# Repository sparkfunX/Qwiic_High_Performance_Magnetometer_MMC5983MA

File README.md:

# SparkX MMC5983MA Magnetometer Breakout

<p align="center">

</p>

*[SparkX Triple Axis Magnetometer - MMC5983MA (Qwiic) (SPX-19034)](https://www.sparkfun.com/products/19034)*

The MMC5983MA is a highly sensitive triple axis magnetometer by MEMSIC.
It is capable of sensing down to 0.4mG enabling a heading accuracy of ±0.5°.
Output rates of 1000Hz, ±8G FSR, and 18-bit resolution make the MMC5983MA a phenomenal magnetic sensor for electronic compass applications.

### Important Note:

An updated version of this product is available:

*[SparkFun 9DoF IMU Breakout - ISM330DHCX, MMC5983MA (Qwiic) (SEN-19895)](https://www.sparkfun.com/products/19895)*

*[SparkFun Micro Magnetometer - MMC5983MA (Qwiic) (SEN-19921)](https://www.sparkfun.com/products/19921)*

## Repository Contents

* **[/Documents](/Documents/)** - MMC5983MA datasheet
* **[/Hardware](/Hardware/)** - Eagle design files (.brd, .sch)

## Product Versions

* [SPX-19034](https://www.sparkfun.com/products/19034) - Initial SparkX Release

## License Information

This product is _**open source**_! 

Please review the LICENSE.md file for license information. 

If you have any questions or concerns on licensing, please contact technical support on our [SparkFun forums](https://forum.sparkfun.com/viewforum.php?f=152).

Distributed as-is; no warranty is given.

- Your friends at SparkFun.

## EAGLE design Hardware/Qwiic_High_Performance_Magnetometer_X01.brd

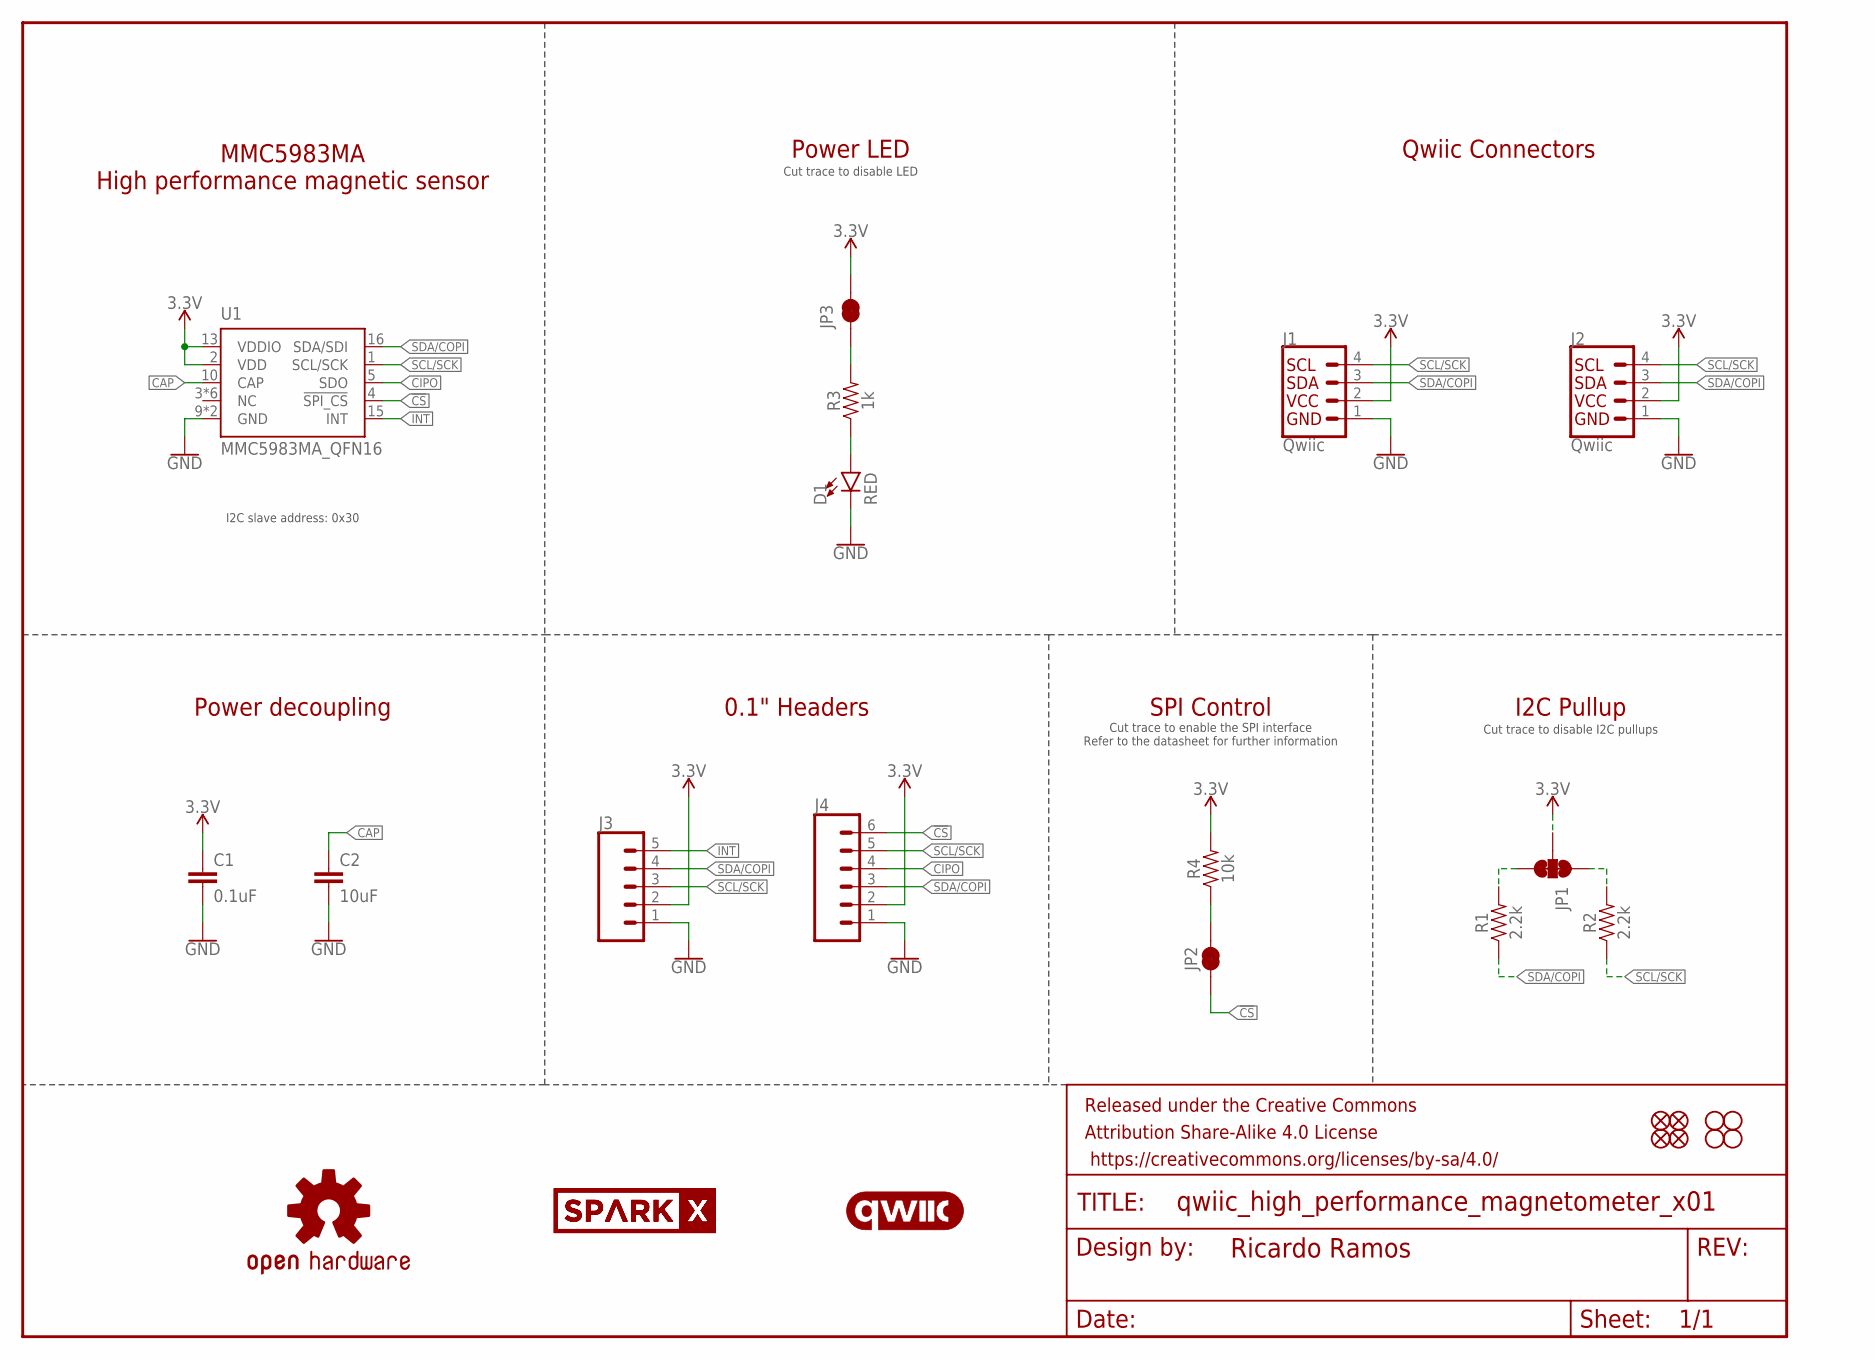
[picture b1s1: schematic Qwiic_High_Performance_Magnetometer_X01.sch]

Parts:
C1: 0.1uF; 0603
C2: 10uF; 0603
D1: RED; LED-0603
FD1, FD2, FD3, FD4: FIDUCIAL1X2; FIDUCIAL-1X2
FRAME1: FRAME-LETTERNO_PACKAGE; DUMMY
H1, H2, H3, H4: STAND-OFF
J1, J2: Qwiic; JST04_1MM_RA
J3: CONN_05NO_SILK; 1X05_NO_SILK
J4: CONN_06NO_SILK_NO_POP; 1X06_NO_SILK
JP1: JUMPER-SMT_3_2-NC_TRACE_SILK; SMT-JUMPER_3_2-NC_TRACE_SILK
JP2, JP3: JUMPER-SMT_2_NC_TRACE_SILK; SMT-JUMPER_2_NC_TRACE_SILK
LOGO1: OSHW-LOGOMINI; OSHW-LOGO-MINI
LOGO2: QWIIC_LOGO_5MM; QWIIC_5MM
R1, R2: 2.2k; 0603
R3: 1k; 0603
R4: 10k; 0603
U1: MMC5983MA_QFN16; LGA-16-3X3MM-4X4PINS
U$36: SPARKX-LOGO2; SPARKX-TINY
U$37: SPARKX-LOGO3; SPARKX-SMALL

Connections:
3.3V: C1.1, J1.2, J2.2, J3.2, J4.2, JP1.2, JP3.2, R4.2, U1.2 (VDD), U1.13 (VDDIO)
!CS!: J4.6, JP2.1, U1.4 (!SPI_CS!)
CAP: C2.1, U1.10 (CAP)
CIPO: J4.4, U1.5 (SDO)
GND: C1.2, C2.2, D1.C, J1.1, J2.1, J3.1, J4.1, U1.9 (GND), U1.11 (GND)
INT: J3.5, U1.15 (INT)
unnamed: JP3.1, R3.2
unnamed: JP1.1, R2.2
unnamed: JP1.3, R1.2
unnamed: D1.A, R3.1
unnamed: JP2.2, R4.1
SCL/SCK: J1.4, J2.4, J3.3, J4.5, R2.1, U1.1 (SCL/SCK)
SDA/COPI: J1.3, J2.3, J3.4, J4.3, R1.1, U1.16 (SDA/SDI)

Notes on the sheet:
Qwiic Connectors
Cut trace to disable LED
0.1" Headers
Power LED
Power decoupling
MMC5983MA High performance magnetic sensor
I2C slave address: 0x30
I2C Pullup
Cut trace to disable I2C pullups
SPI Control
Cut trace to enable the SPI interface Refer to the datasheet for further information

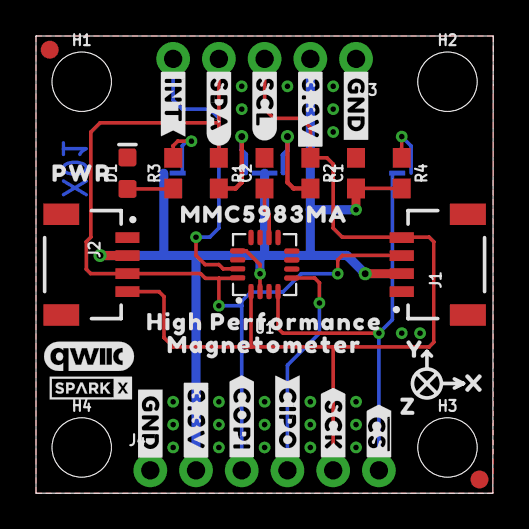
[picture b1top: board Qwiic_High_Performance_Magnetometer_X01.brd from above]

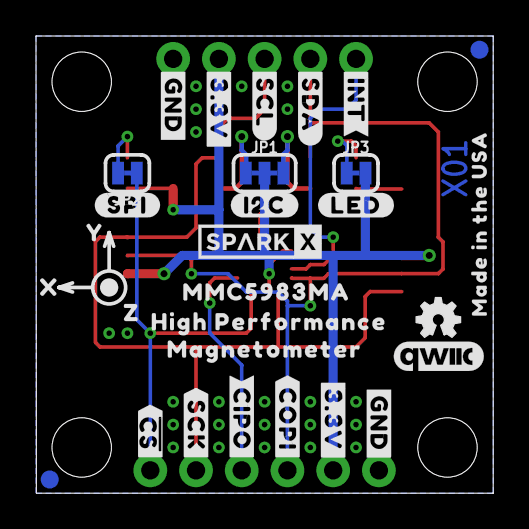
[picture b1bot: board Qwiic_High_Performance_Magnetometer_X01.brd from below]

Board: 2 copper layers, 25.4 x 25.4 mm, 68 parts (29 on the bottom side), 13 nets.

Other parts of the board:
LOGO3: QWIIC_LOGO_5MM; QWIIC_5MM
U$1, U$10: HIGH_PERFORMANCE11
U$2, U$35: #SCL#6
U$3, U$12, U$18, U$29: #3#3V#0
U$4, U$13, U$17, U$28: #GND#4
U$5, U$38: #SDA#5
U$6, U$31: #CIPO#11
U$7, U$16: #INT#7
U$8: PWR9
U$9, U$30: #COPI#12
U$11, U$24: MAGNETOMETER12
U$14, U$32: #SCK#13
U$15, U$33: ##CS##10
U$19, U$26: Y16
U$20, U$25: X15
U$21: #LED#8
U$22: #I2C#9
U$23: #SPI#9
U$27, U$39: Z17
U$34: MADE_IN_THE_USA20
U$41, U$42: MMC5983MA0

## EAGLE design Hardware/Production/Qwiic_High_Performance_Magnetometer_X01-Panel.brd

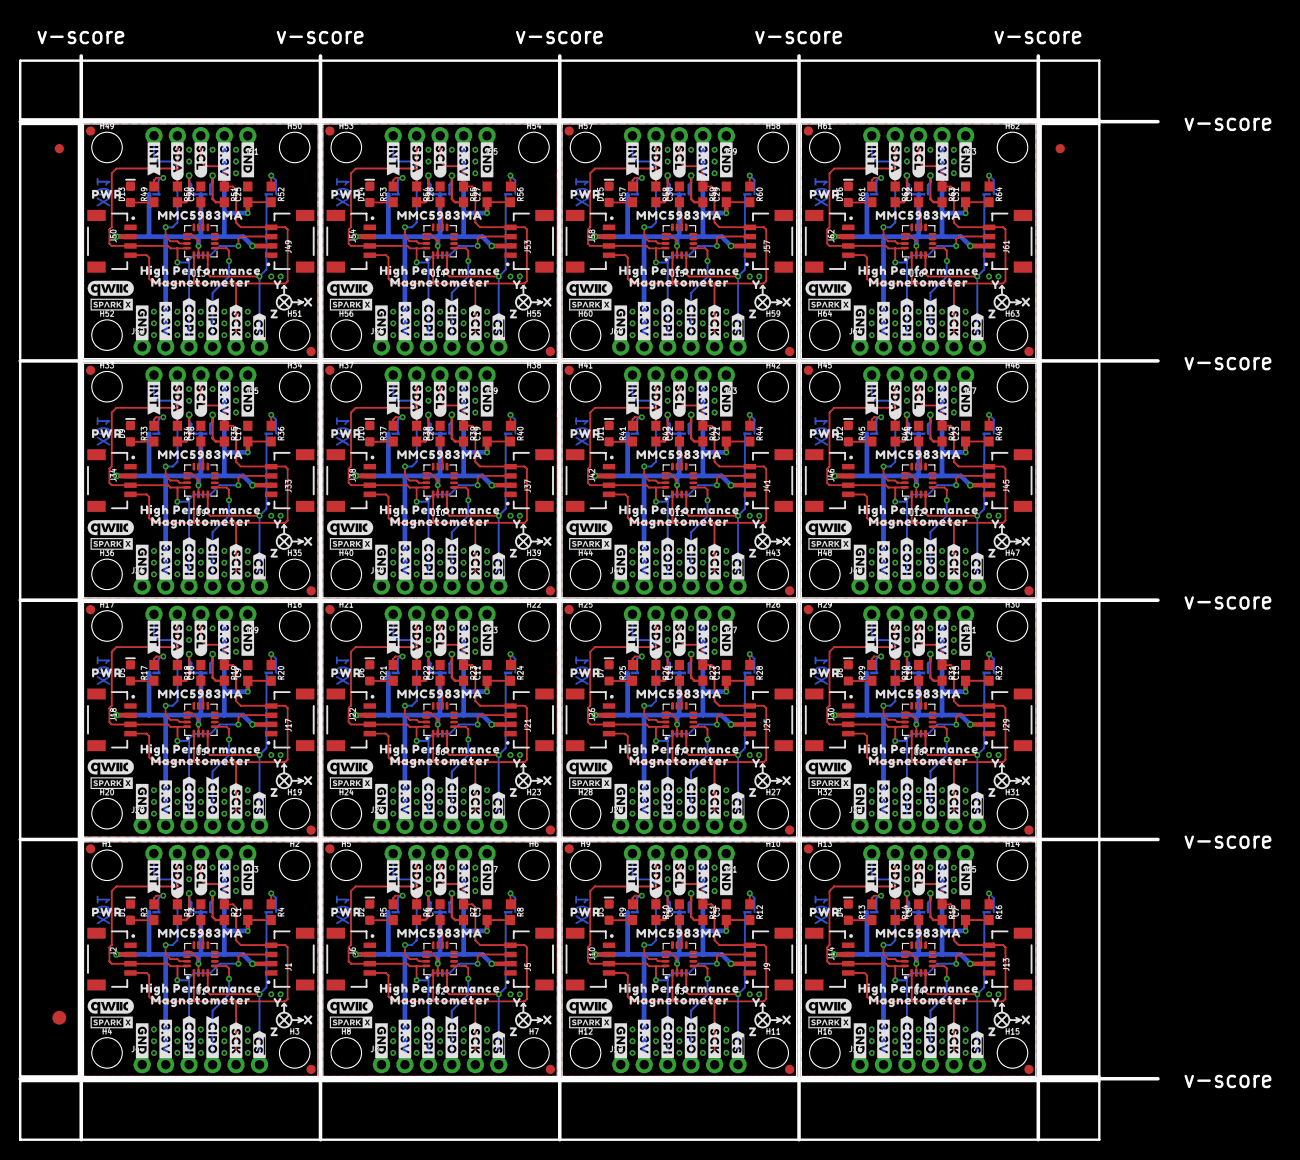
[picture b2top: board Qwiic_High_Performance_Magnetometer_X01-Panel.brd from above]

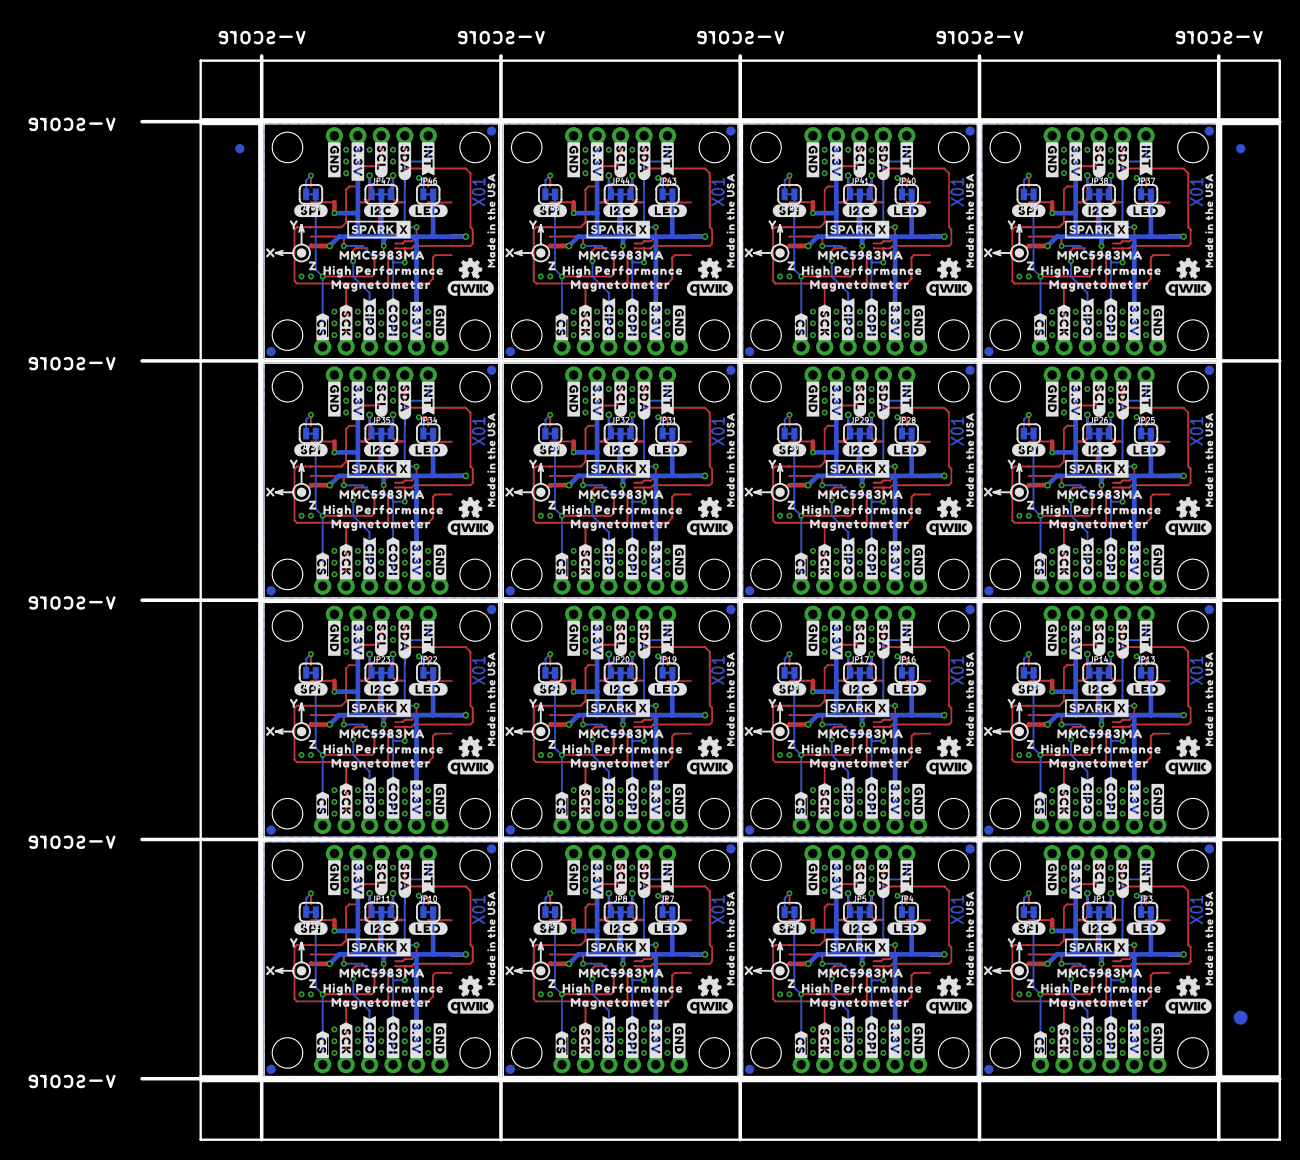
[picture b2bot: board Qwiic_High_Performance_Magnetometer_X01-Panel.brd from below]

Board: 2 copper layers, 123.2 x 117.3 mm, 1094 parts (467 on the bottom side), 208 nets.

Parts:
C1, C3, C5, C7, C9, C11, C13, C15, C17, C19, C21, C23, C25, C27, C29, C31: 0.1uF; 0603
C2, C4, C6, C8, C10, C12, C14, C16, C18, C20, C22, C24, C26, C28, C30, C32: 10uF; 0603
D1, D2, D3, D4, D5, D6, D7, D8, D9, D10, D11, D12, D13, D14, D15, D16: RED; LED-0603
E$1, E$2, E$3, E$4: FIDUCIAL-1X2
E$5, E$6: FIDUCIAL-1.5X3
FD1, FD2, FD3, FD4, FD5, FD6, FD7, FD8, FD9, FD10, FD11, FD12, FD13, FD14, FD15, FD16, FD17, FD18, FD19, FD20, FD21, FD22, FD23, FD24, FD25, FD26, FD27, FD28, FD29, FD30, FD31, FD32, FD33, FD34, FD35, FD36, FD37, FD38, FD39, FD40, FD41, FD42, FD43, FD44, FD45, FD46, FD47, FD48, FD49, FD50, FD51, FD52, FD53, FD54, FD55, FD56, FD57, FD58, FD59, FD60, FD61, FD62, FD63, FD64: FIDUCIAL1X2; FIDUCIAL-1X2
FRAME1, FRAME2, FRAME3, FRAME4, FRAME5, FRAME6, FRAME7, FRAME8, FRAME9, FRAME10, FRAME11, FRAME12, FRAME13, FRAME14, FRAME15, FRAME16: FRAME-LETTERNO_PACKAGE; DUMMY
H1, H2, H3, H4, H5, H6, H7, H8, H9, H10, H11, H12, H13, H14, H15, H16, H17, H18, H19, H20, H21, H22, H23, H24, H25, H26, H27, H28, H29, H30, H31, H32, H33, H34, H35, H36, H37, H38, H39, H40, H41, H42, H43, H44, H45, H46, H47, H48, H49, H50, H51, H52, H53, H54, H55, H56, H57, H58, H59, H60, H61, H62, H63, H64: STAND-OFF
J1, J2, J5, J6, J9, J10, J13, J14, J17, J18, J21, J22, J25, J26, J29, J30, J33, J34, J37, J38, J41, J42, J45, J46, J49, J50, J53, J54, J57, J58, J61, J62: Qwiic; JST04_1MM_RA
J3, J7, J11, J15, J19, J23, J27, J31, J35, J39, J43, J47, J51, J55, J59, J63: 1X05_NO_SILK
J4, J8, J12, J16, J20, J24, J28, J32, J36, J40, J44, J48, J52, J56, J60, J64: 1X06_NO_SILK
JP1, JP5, JP8, JP11, JP14, JP17, JP20, JP23, JP26, JP29, JP32, JP35, JP38, JP41, JP44, JP47: JUMPER-SMT_3_2-NC_TRACE_SILK; SMT-JUMPER_3_2-NC_TRACE_SILK
JP2, JP3, JP4, JP6, JP7, JP9, JP10, JP12, JP13, JP15, JP16, JP18, JP19, JP21, JP22, JP24, JP25, JP27, JP28, JP30, JP31, JP33, JP34, JP36, JP37, JP39, JP40, JP42, JP43, JP45, JP46, JP48: JUMPER-SMT_2_NC_TRACE_SILK; SMT-JUMPER_2_NC_TRACE_SILK
LOGO1, LOGO4, LOGO7, LOGO10, LOGO13, LOGO16, LOGO19, LOGO22, LOGO25, LOGO28, LOGO31, LOGO34, LOGO37, LOGO40, LOGO43, LOGO46: OSHW-LOGOMINI; OSHW-LOGO-MINI
LOGO2, LOGO3, LOGO5, LOGO6, LOGO8, LOGO9, LOGO11, LOGO12, LOGO14, LOGO15, LOGO17, LOGO18, LOGO20, LOGO21, LOGO23, LOGO24, LOGO26, LOGO27, LOGO29, LOGO30, LOGO32, LOGO33, LOGO35, LOGO36, LOGO38, LOGO39, LOGO41, LOGO42, LOGO44, LOGO45, LOGO47, LOGO48: QWIIC_LOGO_5MM; QWIIC_5MM
R1, R2, R6, R7, R10, R11, R14, R15, R18, R19, R22, R23, R26, R27, R30, R31, R34, R35, R38, R39, R42, R43, R46, R47, R50, R51, R54, R55, R58, R59, R62, R63: 2.2k; 0603
R3, R5, R9, R13, R17, R21, R25, R29, R33, R37, R41, R45, R49, R53, R57, R61: 1k; 0603
R4, R8, R12, R16, R20, R24, R28, R32, R36, R40, R44, R48, R52, R56, R60, R64: 10k; 0603
U1, U2, U3, U4, U5, U6, U7, U8, U9, U10, U11, U12, U13, U14, U15, U16: MMC5893MA_QFN16; LGA-16-3X3MM-4X4PINS
U$1, U$10, U$46, U$67, U$87, U$108, U$128, U$149, U$169, U$190, U$210, U$231, U$251, U$272, U$292, U$313, U$333, U$354, U$374, U$395, U$415, U$436, U$456, U$477, U$497, U$518, U$538, U$559, U$579, U$600, U$620, U$641: HIGH_PERFORMANCE11
U$2, U$35, U$54, U$78, U$95, U$119, U$136, U$160, U$177, U$201, U$218, U$242, U$259, U$283, U$300, U$324, U$341, U$365, U$382, U$406, U$423, U$447, U$464, U$488, U$505, U$529, U$546, U$570, U$587, U$611, U$628, U$652: #SCL#6
U$3, U$12, U$18, U$29, U$40, U$48, U$60, U$70, U$83, U$89, U$101, U$111, U$124, U$130, U$142, U$152, U$165, U$171, U$183, U$193, U$206, U$212, U$224, U$234, U$247, U$253, U$265, U$275, U$288, U$294, U$306, U$316, U$329, U$335, U$347, U$357, U$370, U$376, U$388, U$398, U$411, U$417, U$429, U$439, U$452, U$458, U$470, U$480, U$493, U$499, U$511, U$521, U$534, U$540, U$552, U$562, U$575, U$581, U$593, U$603, U$616, U$622, U$634, U$644: #3#3V#0
U$4, U$13, U$17, U$28, U$43, U$49, U$66, U$69, U$84, U$90, U$107, U$110, U$125, U$131, U$148, U$151, U$166, U$172, U$189, U$192, U$207, U$213, U$230, U$233, U$248, U$254, U$271, U$274, U$289, U$295, U$312, U$315, U$330, U$336, U$353, U$356, U$371, U$377, U$394, U$397, U$412, U$418, U$435, U$438, U$453, U$459, U$476, U$479, U$494, U$500, U$517, U$520, U$535, U$541, U$558, U$561, U$576, U$582, U$599, U$602, U$617, U$623, U$640, U$643: #GND#4
U$5, U$38, U$55, U$79, U$96, U$120, U$137, U$161, U$178, U$202, U$219, U$243, U$260, U$284, U$301, U$325, U$342, U$366, U$383, U$407, U$424, U$448, U$465, U$489, U$506, U$530, U$547, U$571, U$588, U$612, U$629, U$653: #SDA#5
U$6, U$31, U$56, U$72, U$97, U$113, U$138, U$154, U$179, U$195, U$220, U$236, U$261, U$277, U$302, U$318, U$343, U$359, U$384, U$400, U$425, U$441, U$466, U$482, U$507, U$523, U$548, U$564, U$589, U$605, U$630, U$646: #CIPO#11
U$7, U$16, U$44, U$50, U$85, U$91, U$126, U$132, U$167, U$173, U$208, U$214, U$249, U$255, U$290, U$296, U$331, U$337, U$372, U$378, U$413, U$419, U$454, U$460, U$495, U$501, U$536, U$542, U$577, U$583, U$618, U$624: #INT#7
U$8, U$45, U$86, U$127, U$168, U$209, U$250, U$291, U$332, U$373, U$414, U$455, U$496, U$537, U$578, U$619: PWR9
U$9, U$30, U$57, U$71, U$98, U$112, U$139, U$153, U$180, U$194, U$221, U$235, U$262, U$276, U$303, U$317, U$344, U$358, U$385, U$399, U$426, U$440, U$467, U$481, U$508, U$522, U$549, U$563, U$590, U$604, U$631, U$645: #COPI#12
U$11, U$24, U$47, U$68, U$88, U$109, U$129, U$150, U$170, U$191, U$211, U$232, U$252, U$273, U$293, U$314, U$334, U$355, U$375, U$396, U$416, U$437, U$457, U$478, U$498, U$519, U$539, U$560, U$580, U$601, U$621, U$642: MAGNETOMETER12
U$14, U$32, U$58, U$73, U$99, U$114, U$140, U$155, U$181, U$196, U$222, U$237, U$263, U$278, U$304, U$319, U$345, U$360, U$386, U$401, U$427, U$442, U$468, U$483, U$509, U$524, U$550, U$565, U$591, U$606, U$632, U$647: #SCK#13
U$15, U$33, U$59, U$74, U$100, U$115, U$141, U$156, U$182, U$197, U$223, U$238, U$264, U$279, U$305, U$320, U$346, U$361, U$387, U$402, U$428, U$443, U$469, U$484, U$510, U$525, U$551, U$566, U$592, U$607, U$633, U$648: ##CS##10
U$19, U$26, U$61, U$64, U$102, U$105, U$143, U$146, U$184, U$187, U$225, U$228, U$266, U$269, U$307, U$310, U$348, U$351, U$389, U$392, U$430, U$433, U$471, U$474, U$512, U$515, U$553, U$556, U$594, U$597, U$635, U$638: Y16
U$20, U$25, U$62, U$63, U$103, U$104, U$144, U$145, U$185, U$186, U$226, U$227, U$267, U$268, U$308, U$309, U$349, U$350, U$390, U$391, U$431, U$432, U$472, U$473, U$513, U$514, U$554, U$555, U$595, U$596, U$636, U$637: X15
U$21, U$51, U$92, U$133, U$174, U$215, U$256, U$297, U$338, U$379, U$420, U$461, U$502, U$543, U$584, U$625: #LED#8
U$22, U$52, U$93, U$134, U$175, U$216, U$257, U$298, U$339, U$380, U$421, U$462, U$503, U$544, U$585, U$626: #I2C#9
U$23, U$53, U$94, U$135, U$176, U$217, U$258, U$299, U$340, U$381, U$422, U$463, U$504, U$545, U$586, U$627: #SPI#9
U$27, U$39, U$65, U$80, U$106, U$121, U$147, U$162, U$188, U$203, U$229, U$244, U$270, U$285, U$311, U$326, U$352, U$367, U$393, U$408, U$434, U$449, U$475, U$490, U$516, U$531, U$557, U$572, U$598, U$613, U$639, U$654: Z17
U$34, U$77, U$118, U$159, U$200, U$241, U$282, U$323, U$364, U$405, U$446, U$487, U$528, U$569, U$610, U$651: MADE_IN_THE_USA20
U$36, U$75, U$116, U$157, U$198, U$239, U$280, U$321, U$362, U$403, U$444, U$485, U$526, U$567, U$608, U$649: SPARKX-LOGO2; SPARKX-TINY
U$37, U$76, U$117, U$158, U$199, U$240, U$281, U$322, U$363, U$404, U$445, U$486, U$527, U$568, U$609, U$650: SPARKX-LOGO3; SPARKX-SMALL
U$41, U$42, U$81, U$82, U$122, U$123, U$163, U$164, U$204, U$205, U$245, U$246, U$286, U$287, U$327, U$328, U$368, U$369, U$409, U$410, U$450, U$451, U$491, U$492, U$532, U$533, U$573, U$574, U$614, U$615, U$655, U$656: MMC5983MA0

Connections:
3.3V: C1.1, J1.2, J2.2, J3.2, J4.2, JP1.2, JP3.2, R4.2, U1.2, U1.13
3.3V1: C3.1, J5.2, J6.2, J7.2, J8.2, JP4.2, JP5.2, R8.2, U2.2, U2.13
3.3V2: C5.1, J9.2, J10.2, J11.2, J12.2, JP7.2, JP8.2, R12.2, U3.2, U3.13
3.3V3: C7.1, J13.2, J14.2, J15.2, J16.2, JP10.2, JP11.2, R16.2, U4.2, U4.13
3.3V4: C9.1, J17.2, J18.2, J19.2, J20.2, JP13.2, JP14.2, R20.2, U5.2, U5.13
3.3V5: C11.1, J21.2, J22.2, J23.2, J24.2, JP16.2, JP17.2, R24.2, U6.2, U6.13
3.3V6: C13.1, J25.2, J26.2, J27.2, J28.2, JP19.2, JP20.2, R28.2, U7.2, U7.13
3.3V7: C15.1, J29.2, J30.2, J31.2, J32.2, JP22.2, JP23.2, R32.2, U8.2, U8.13
3.3V8: C17.1, J33.2, J34.2, J35.2, J36.2, JP25.2, JP26.2, R36.2, U9.2, U9.13
3.3V9: C19.1, J37.2, J38.2, J39.2, J40.2, JP28.2, JP29.2, R40.2, U10.2, U10.13
3.3V10: C21.1, J41.2, J42.2, J43.2, J44.2, JP31.2, JP32.2, R44.2, U11.2, U11.13
3.3V11: C23.1, J45.2, J46.2, J47.2, J48.2, JP34.2, JP35.2, R48.2, U12.2, U12.13
3.3V12: C25.1, J49.2, J50.2, J51.2, J52.2, JP37.2, JP38.2, R52.2, U13.2, U13.13
3.3V13: C27.1, J53.2, J54.2, J55.2, J56.2, JP40.2, JP41.2, R56.2, U14.2, U14.13
3.3V14: C29.1, J57.2, J58.2, J59.2, J60.2, JP43.2, JP44.2, R60.2, U15.2, U15.13
3.3V15: C31.1, J61.2, J62.2, J63.2, J64.2, JP46.2, JP47.2, R64.2, U16.2, U16.13
!CS!: J4.6, JP2.1, U1.4
!CS!1: J8.6, JP6.1, U2.4
!CS!2: J12.6, JP9.1, U3.4
!CS!3: J16.6, JP12.1, U4.4
!CS!4: J20.6, JP15.1, U5.4
!CS!5: J24.6, JP18.1, U6.4
!CS!6: J28.6, JP21.1, U7.4
!CS!7: J32.6, JP24.1, U8.4
!CS!8: J36.6, JP27.1, U9.4
!CS!9: J40.6, JP30.1, U10.4
!CS!10: J44.6, JP33.1, U11.4
!CS!11: J48.6, JP36.1, U12.4
!CS!12: J52.6, JP39.1, U13.4
!CS!13: J56.6, JP42.1, U14.4
!CS!14: J60.6, JP45.1, U15.4
!CS!15: J64.6, JP48.1, U16.4
CAP: C2.1, U1.10
CAP1: C4.1, U2.10
CAP2: C6.1, U3.10
CAP3: C8.1, U4.10
CAP4: C10.1, U5.10
CAP5: C12.1, U6.10
CAP6: C14.1, U7.10
CAP7: C16.1, U8.10
CAP8: C18.1, U9.10
CAP9: C20.1, U10.10
CAP10: C22.1, U11.10
CAP11: C24.1, U12.10
CAP12: C26.1, U13.10
CAP13: C28.1, U14.10
CAP14: C30.1, U15.10
CAP15: C32.1, U16.10
CIPO: J4.4, U1.5
CIPO1: J8.4, U2.5
CIPO2: J12.4, U3.5
CIPO3: J16.4, U4.5
CIPO4: J20.4, U5.5
CIPO5: J24.4, U6.5
CIPO6: J28.4, U7.5
CIPO7: J32.4, U8.5
CIPO8: J36.4, U9.5
CIPO9: J40.4, U10.5
CIPO10: J44.4, U11.5
CIPO11: J48.4, U12.5
CIPO12: J52.4, U13.5
CIPO13: J56.4, U14.5
CIPO14: J60.4, U15.5
CIPO15: J64.4, U16.5
GND: C1.2, C2.2, D1.C, J1.1, J2.1, J3.1, J4.1, U1.9, U1.11
GND1: C3.2, C4.2, D2.C, J5.1, J6.1, J7.1, J8.1, U2.9, U2.11
GND2: C5.2, C6.2, D3.C, J9.1, J10.1, J11.1, J12.1, U3.9, U3.11
GND3: C7.2, C8.2, D4.C, J13.1, J14.1, J15.1, J16.1, U4.9, U4.11
GND4: C9.2, C10.2, D5.C, J17.1, J18.1, J19.1, J20.1, U5.9, U5.11
GND5: C11.2, C12.2, D6.C, J21.1, J22.1, J23.1, J24.1, U6.9, U6.11
GND6: C13.2, C14.2, D7.C, J25.1, J26.1, J27.1, J28.1, U7.9, U7.11
GND7: C15.2, C16.2, D8.C, J29.1, J30.1, J31.1, J32.1, U8.9, U8.11
GND8: C17.2, C18.2, D9.C, J33.1, J34.1, J35.1, J36.1, U9.9, U9.11
GND9: C19.2, C20.2, D10.C, J37.1, J38.1, J39.1, J40.1, U10.9, U10.11
GND10: C21.2, C22.2, D11.C, J41.1, J42.1, J43.1, J44.1, U11.9, U11.11
GND11: C23.2, C24.2, D12.C, J45.1, J46.1, J47.1, J48.1, U12.9, U12.11
GND12: C25.2, C26.2, D13.C, J49.1, J50.1, J51.1, J52.1, U13.9, U13.11
GND13: C27.2, C28.2, D14.C, J53.1, J54.1, J55.1, J56.1, U14.9, U14.11
GND14: C29.2, C30.2, D15.C, J57.1, J58.1, J59.1, J60.1, U15.9, U15.11
GND15: C31.2, C32.2, D16.C, J61.1, J62.1, J63.1, J64.1, U16.9, U16.11
INT: J3.5, U1.15
INT1: J7.5, U2.15
INT2: J11.5, U3.15
INT3: J15.5, U4.15
INT4: J19.5, U5.15
INT5: J23.5, U6.15
INT6: J27.5, U7.15
INT7: J31.5, U8.15
INT8: J35.5, U9.15
INT9: J39.5, U10.15
INT10: J43.5, U11.15
INT11: J47.5, U12.15
INT12: J51.5, U13.15
INT13: J55.5, U14.15
INT14: J59.5, U15.15
INT15: J63.5, U16.15
unnamed: JP3.1, R3.2
unnamed: JP1.1, R2.2
unnamed: JP1.3, R1.2
unnamed: D1.A, R3.1
unnamed: JP2.2, R4.1
unnamed: JP4.1, R5.2
unnamed: D2.A, R5.1
unnamed: JP5.1, R7.2
unnamed: JP5.3, R6.2
unnamed: JP6.2, R8.1
unnamed: JP7.1, R9.2
unnamed: D3.A, R9.1
unnamed: JP8.1, R11.2
unnamed: JP8.3, R10.2
unnamed: JP9.2, R12.1
unnamed: JP10.1, R13.2
unnamed: D4.A, R13.1
unnamed: JP11.1, R15.2
unnamed: JP11.3, R14.2
unnamed: JP12.2, R16.1
unnamed: JP13.1, R17.2
unnamed: D5.A, R17.1
unnamed: JP14.1, R19.2
unnamed: JP14.3, R18.2
unnamed: JP15.2, R20.1
unnamed: JP16.1, R21.2
unnamed: D6.A, R21.1
unnamed: JP17.1, R23.2
unnamed: JP17.3, R22.2
unnamed: JP18.2, R24.1
unnamed: JP19.1, R25.2
unnamed: D7.A, R25.1
unnamed: JP20.1, R27.2
unnamed: JP20.3, R26.2
unnamed: JP21.2, R28.1
unnamed: JP22.1, R29.2
unnamed: D8.A, R29.1
unnamed: JP23.1, R31.2
unnamed: JP23.3, R30.2
unnamed: JP24.2, R32.1
unnamed: JP25.1, R33.2
unnamed: D9.A, R33.1
unnamed: JP26.1, R35.2
unnamed: JP26.3, R34.2
unnamed: JP27.2, R36.1
unnamed: JP28.1, R37.2
unnamed: D10.A, R37.1
unnamed: JP29.1, R39.2
unnamed: JP29.3, R38.2
unnamed: JP30.2, R40.1
unnamed: JP31.1, R41.2
unnamed: D11.A, R41.1
unnamed: JP32.1, R43.2
unnamed: JP32.3, R42.2
unnamed: JP33.2, R44.1
unnamed: JP34.1, R45.2
unnamed: D12.A, R45.1
unnamed: JP35.1, R47.2
unnamed: JP35.3, R46.2
unnamed: JP36.2, R48.1
unnamed: JP37.1, R49.2
unnamed: D13.A, R49.1
unnamed: JP38.1, R51.2
unnamed: JP38.3, R50.2
unnamed: JP39.2, R52.1
unnamed: JP40.1, R53.2
unnamed: D14.A, R53.1
unnamed: JP41.1, R55.2
unnamed: JP41.3, R54.2
unnamed: JP42.2, R56.1
unnamed: JP43.1, R57.2
unnamed: D15.A, R57.1
unnamed: JP44.1, R59.2
unnamed: JP44.3, R58.2
unnamed: JP45.2, R60.1
unnamed: JP46.1, R61.2
unnamed: D16.A, R61.1
unnamed: JP47.1, R63.2
unnamed: JP47.3, R62.2
unnamed: JP48.2, R64.1
SCL/SCK: J1.4, J2.4, J3.3, J4.5, R2.1, U1.1
SCL/SCK1: J5.4, J6.4, J7.3, J8.5, R7.1, U2.1
SCL/SCK2: J9.4, J10.4, J11.3, J12.5, R11.1, U3.1
SCL/SCK3: J13.4, J14.4, J15.3, J16.5, R15.1, U4.1
SCL/SCK4: J17.4, J18.4, J19.3, J20.5, R19.1, U5.1
SCL/SCK5: J21.4, J22.4, J23.3, J24.5, R23.1, U6.1
SCL/SCK6: J25.4, J26.4, J27.3, J28.5, R27.1, U7.1
SCL/SCK7: J29.4, J30.4, J31.3, J32.5, R31.1, U8.1
SCL/SCK8: J33.4, J34.4, J35.3, J36.5, R35.1, U9.1
SCL/SCK9: J37.4, J38.4, J39.3, J40.5, R39.1, U10.1
SCL/SCK10: J41.4, J42.4, J43.3, J44.5, R43.1, U11.1
SCL/SCK11: J45.4, J46.4, J47.3, J48.5, R47.1, U12.1
SCL/SCK12: J49.4, J50.4, J51.3, J52.5, R51.1, U13.1
SCL/SCK13: J53.4, J54.4, J55.3, J56.5, R55.1, U14.1
SCL/SCK14: J57.4, J58.4, J59.3, J60.5, R59.1, U15.1
SCL/SCK15: J61.4, J62.4, J63.3, J64.5, R63.1, U16.1
SDA/COPI: J1.3, J2.3, J3.4, J4.3, R1.1, U1.16
SDA/COPI1: J5.3, J6.3, J7.4, J8.3, R6.1, U2.16
SDA/COPI2: J9.3, J10.3, J11.4, J12.3, R10.1, U3.16
SDA/COPI3: J13.3, J14.3, J15.4, J16.3, R14.1, U4.16
SDA/COPI4: J17.3, J18.3, J19.4, J20.3, R18.1, U5.16
SDA/COPI5: J21.3, J22.3, J23.4, J24.3, R22.1, U6.16
SDA/COPI6: J25.3, J26.3, J27.4, J28.3, R26.1, U7.16
SDA/COPI7: J29.3, J30.3, J31.4, J32.3, R30.1, U8.16
SDA/COPI8: J33.3, J34.3, J35.4, J36.3, R34.1, U9.16
SDA/COPI9: J37.3, J38.3, J39.4, J40.3, R38.1, U10.16
SDA/COPI10: J41.3, J42.3, J43.4, J44.3, R42.1, U11.16
SDA/COPI11: J45.3, J46.3, J47.4, J48.3, R46.1, U12.16
SDA/COPI12: J49.3, J50.3, J51.4, J52.3, R50.1, U13.16
SDA/COPI13: J53.3, J54.3, J55.4, J56.3, R54.1, U14.16
SDA/COPI14: J57.3, J58.3, J59.4, J60.3, R58.1, U15.16
SDA/COPI15: J61.3, J62.3, J63.4, J64.3, R62.1, U16.16

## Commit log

2021-11-04 Initial version uploaded.
2021-11-04 Created production files
2021-11-09 Added SPI breakout header; created PCB production files.
2021-11-09 Fixed SPI header alignment.
2021-11-09 Improved top ground plane under the IC.
2021-11-09 Renamed file to reflect version. Added PCB version to bottom silk.
2021-11-09 Added bom csv file.
2021-11-24 Added production files; updated BOM.
2021-12-03 Fixed typo

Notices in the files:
README.md:
License: CC BY-SA 4.0
parts and their libraries:
SparkFun-Capacitors: Licensing: Creative Commons ShareAlike 4.0 International - https://creativecommons.org/licenses/by-sa/4.0
SparkFun-Aesthetics: Released under the Creative Commons Attribution Share-Alike 4.0 License
SparkFun-Aesthetics: https://creativecommons.org/licenses/by-sa/4.0
